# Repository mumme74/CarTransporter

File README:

Abstraction layer for EEPROM ICs like 25AA/25LC (SPI).

1. DESCRIPTION

This library designed to work on top of ChibiOS/RT. It abstracts access to
EEPROM like a regular file(s).

2. LIMITATIONS

* SPI Only.

3. USAGE

* Include eeprom.h file to your project.
* Modify eeprom_conf.h for your project.
* Define file object of an EepromFileStream type and config structure for it.
* Open it with EepromOpen() function.

Now you can access to EEPROM array like to a regular file with functions:
- chFileStreamRead()
- chFileStreamWrite()
- chFileStreamGetPosition()
- chFileStreamSeek()
etc.

Examples of usage and checking the returning parameter you can found in
eeprom_testsuit.c

Based on 24aa project of ChibiOS/RT from Uladzimir Pylinski (aka barthess):
https://github.com/barthess/24aa

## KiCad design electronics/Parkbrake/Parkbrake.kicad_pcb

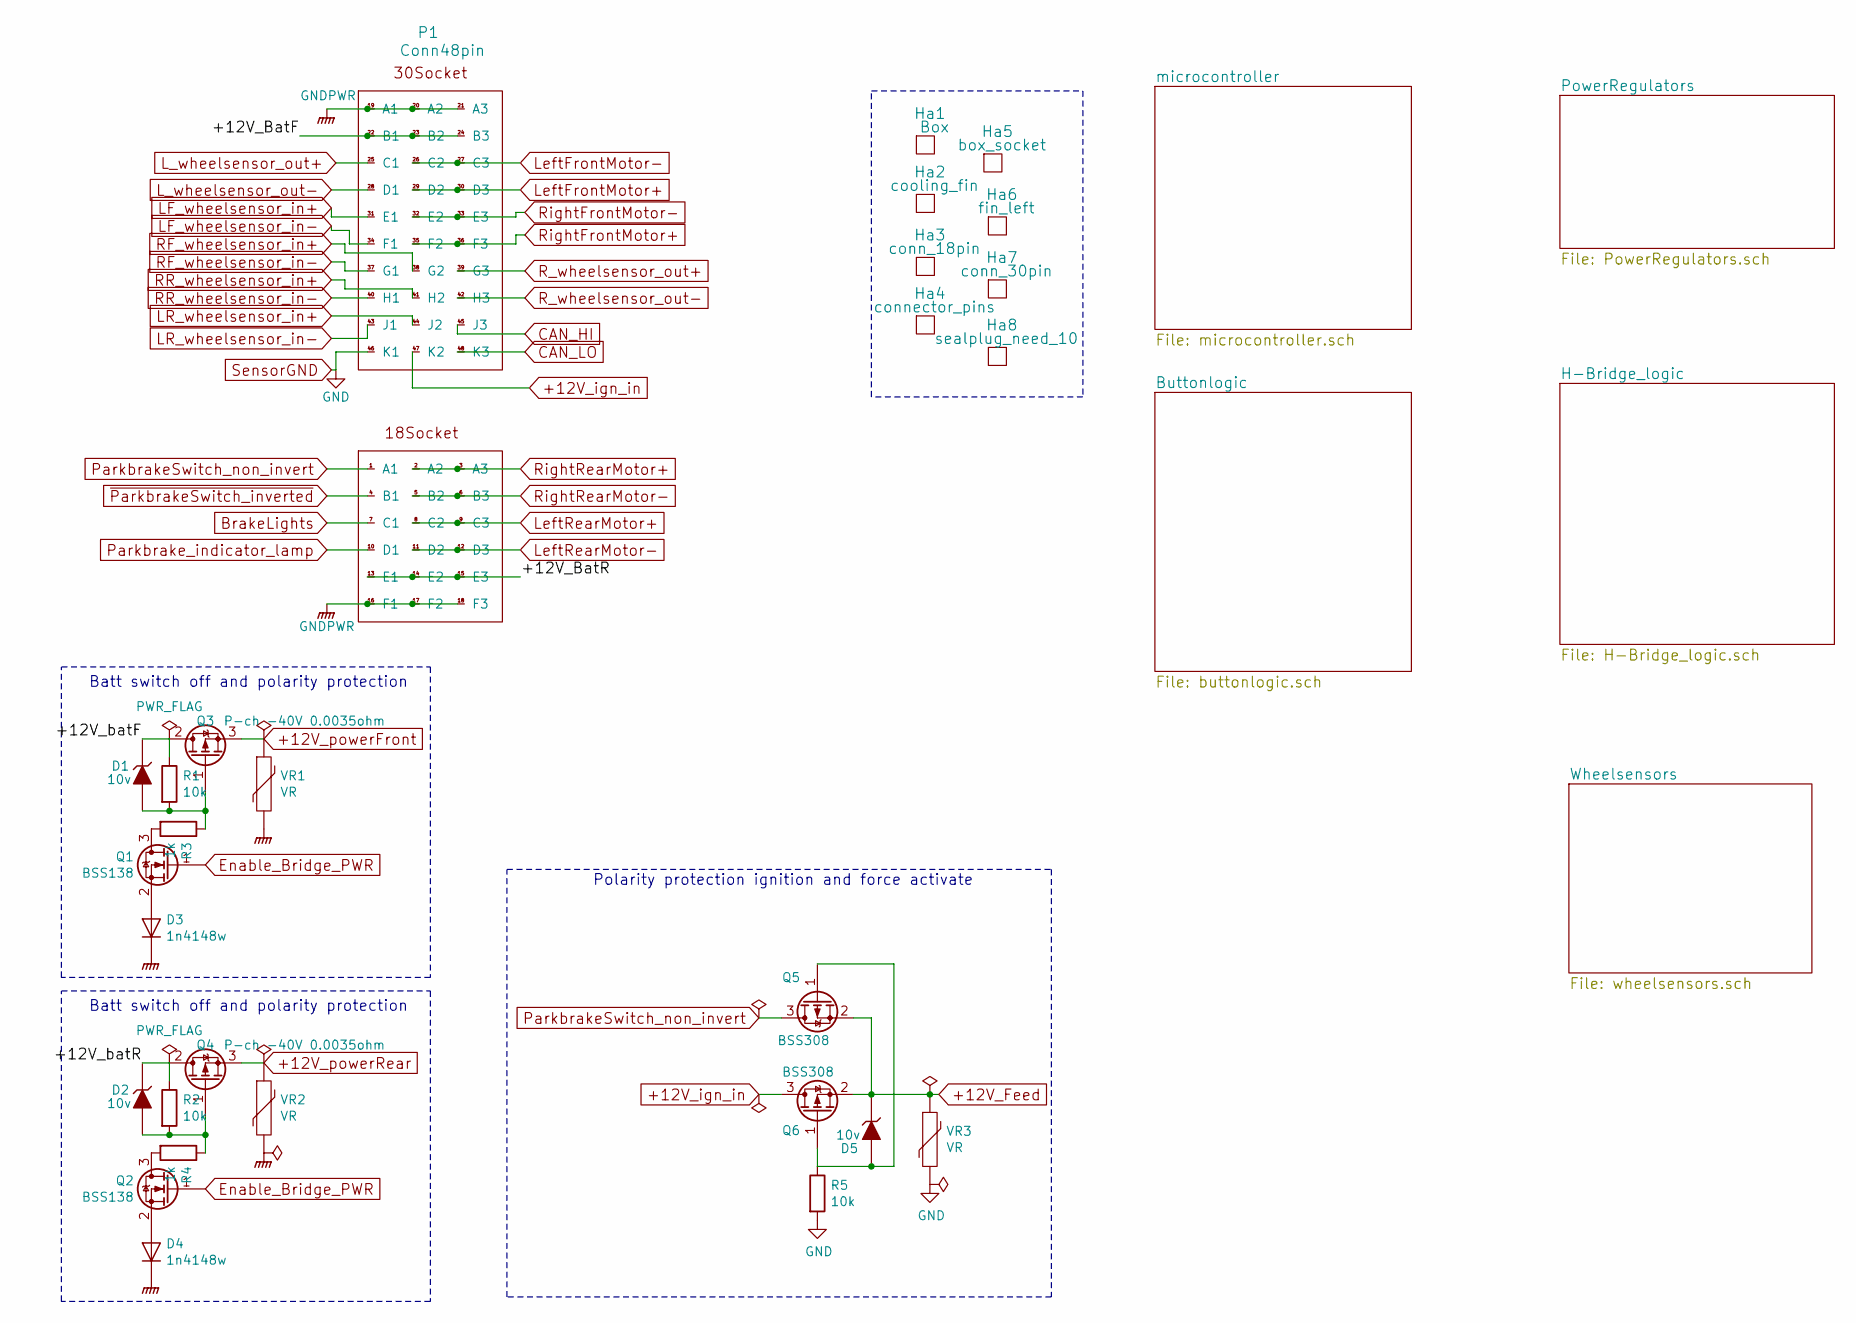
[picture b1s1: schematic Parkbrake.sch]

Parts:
D1, D2, D5: 10v; SOD-323; part MM3Z10VT1G; farnell 1431190
D3, D4: 1n4148w; SOD-323; part 1N4148WS; farnell 1466524
Ha1: Box; part 5810130042; farnell 1282197
Ha2: cooling_fin; part 5810000021; farnell 1282203
Ha3: conn_18pin; part 581-01-18-023; farnell 2099333
Ha4: connector_pins; part 4250000872; farnell 1282209
Ha5: box_socket; part 5810148007; farnell 1282184
Ha6: fin_left; part 5810000020; farnell 1282204
Ha7: conn_30pin; part 581-01-30-029; farnell 2143771
Ha8: sealplug_need_10; part 581-00-00-011; farnell 2099332
P1: Conn48pin
Q1, Q2: BSS138; SOT-323; part BSS138PW; farnell 1907611
Q3, Q4: P-ch -40V 0.0035ohm; TO-252-2Lead; part PD90P04P4-05; farnell 2480840
Q5, Q6: BSS308; SOT-23; part BSS308PE H6327; farnell 2432719
R1, R2, R5: 10k; R_0805; part MC01W0805110K; farnell 9332391
R3, R4: 1k; R_0805; part MC01W080511K; farnell 9332383
VR1, VR2, VR3: VR; R_1206; part VCAS120614A300DP; farnell 2346678

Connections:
+12V_Feed: D5.1 (K), Q5.2 (S), Q6.2 (S), VR3.1; also elsewhere on the board
+12V_ign_in: P1.47 (K2), Q6.3 (D); also elsewhere on the board
+12V_powerFront: Q3.3 (S), VR1.1; also elsewhere on the board
+12V_powerRear: Q4.3 (S), VR2.1; also elsewhere on the board
/+12V_BatF: D1.1 (K), P1.22 (B1), P1.23 (B2), P1.24 (B3), Q3.2 (D), R1.1
/+12V_BatR: D2.1 (K), P1.13 (E1), P1.14 (E2), P1.15 (E3), Q4.2 (D), R2.1
BrakeLights: P1.7 (C1); also elsewhere on the board
CAN_HI: P1.45 (J3); also elsewhere on the board
CAN_LO: P1.48 (K3); also elsewhere on the board
Enable_Bridge_PWR: Q1.1 (G), Q2.1 (G); also elsewhere on the board
GNDPWR: D3.1 (K), D4.1 (K), P1.16 (F1), P1.17 (F2), P1.18 (F3), P1.19 (A1), P1.20 (A2), P1.21 (A3), VR1.2, VR2.2; also elsewhere on the board
LF_wheelsensor_in+: P1.31 (E1); also elsewhere on the board
LF_wheelsensor_in-: P1.34 (F1); also elsewhere on the board
LR_wheelsensor_in+: P1.44 (J2); also elsewhere on the board
LR_wheelsensor_in-: P1.40 (H1), P1.43 (J1), P1.46 (K1), R5.2, VR3.2; also elsewhere on the board
L_wheelsensor_out+: P1.25 (C1); also elsewhere on the board
L_wheelsensor_out-: P1.28 (D1); also elsewhere on the board
LeftFrontMotor+: P1.29 (D2), P1.30 (D3); also elsewhere on the board
LeftFrontMotor-: P1.26 (C2), P1.27 (C3); also elsewhere on the board
LeftRearMotor+: P1.8 (C2), P1.9 (C3); also elsewhere on the board
LeftRearMotor-: P1.11 (D2), P1.12 (D3); also elsewhere on the board
unnamed: D1.2 (A), Q3.1 (G), R1.2, R3.1
unnamed: D2.2 (A), Q4.1 (G), R2.2, R4.1
unnamed: D3.2 (A), Q1.2 (S)
unnamed: D4.2 (A), Q2.2 (S)
unnamed: D5.2 (A), Q5.1 (G), Q6.1 (G), R5.1
unnamed: Q1.3 (D), R3.2
unnamed: Q2.3 (D), R4.2
ParkbrakeSwitch_non_invert: P1.1 (A1), Q5.3 (D); also elsewhere on the board
Parkbrake_indicator_lamp: P1.10 (D1); also elsewhere on the board
RF_wheelsensor_in+: P1.38 (G2); also elsewhere on the board
RF_wheelsensor_in-: P1.37 (G1); also elsewhere on the board
RR_wheelsensor_in+: P1.41 (H2); also elsewhere on the board
R_wheelsensor_out+: P1.39 (G3); also elsewhere on the board
R_wheelsensor_out-: P1.42 (H3); also elsewhere on the board
RightFrontMotor+: P1.35 (F2), P1.36 (F3); also elsewhere on the board
RightFrontMotor-: P1.32 (E2), P1.33 (E3); also elsewhere on the board
RightRearMotor+: P1.2 (A2), P1.3 (A3); also elsewhere on the board
RightRearMotor-: P1.5 (B2), P1.6 (B3); also elsewhere on the board
~ParkbrakeSwitch_inverted: P1.4 (B1); also elsewhere on the board

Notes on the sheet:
Batt switch off and polarity protection
Polarity protection ignition and force activate

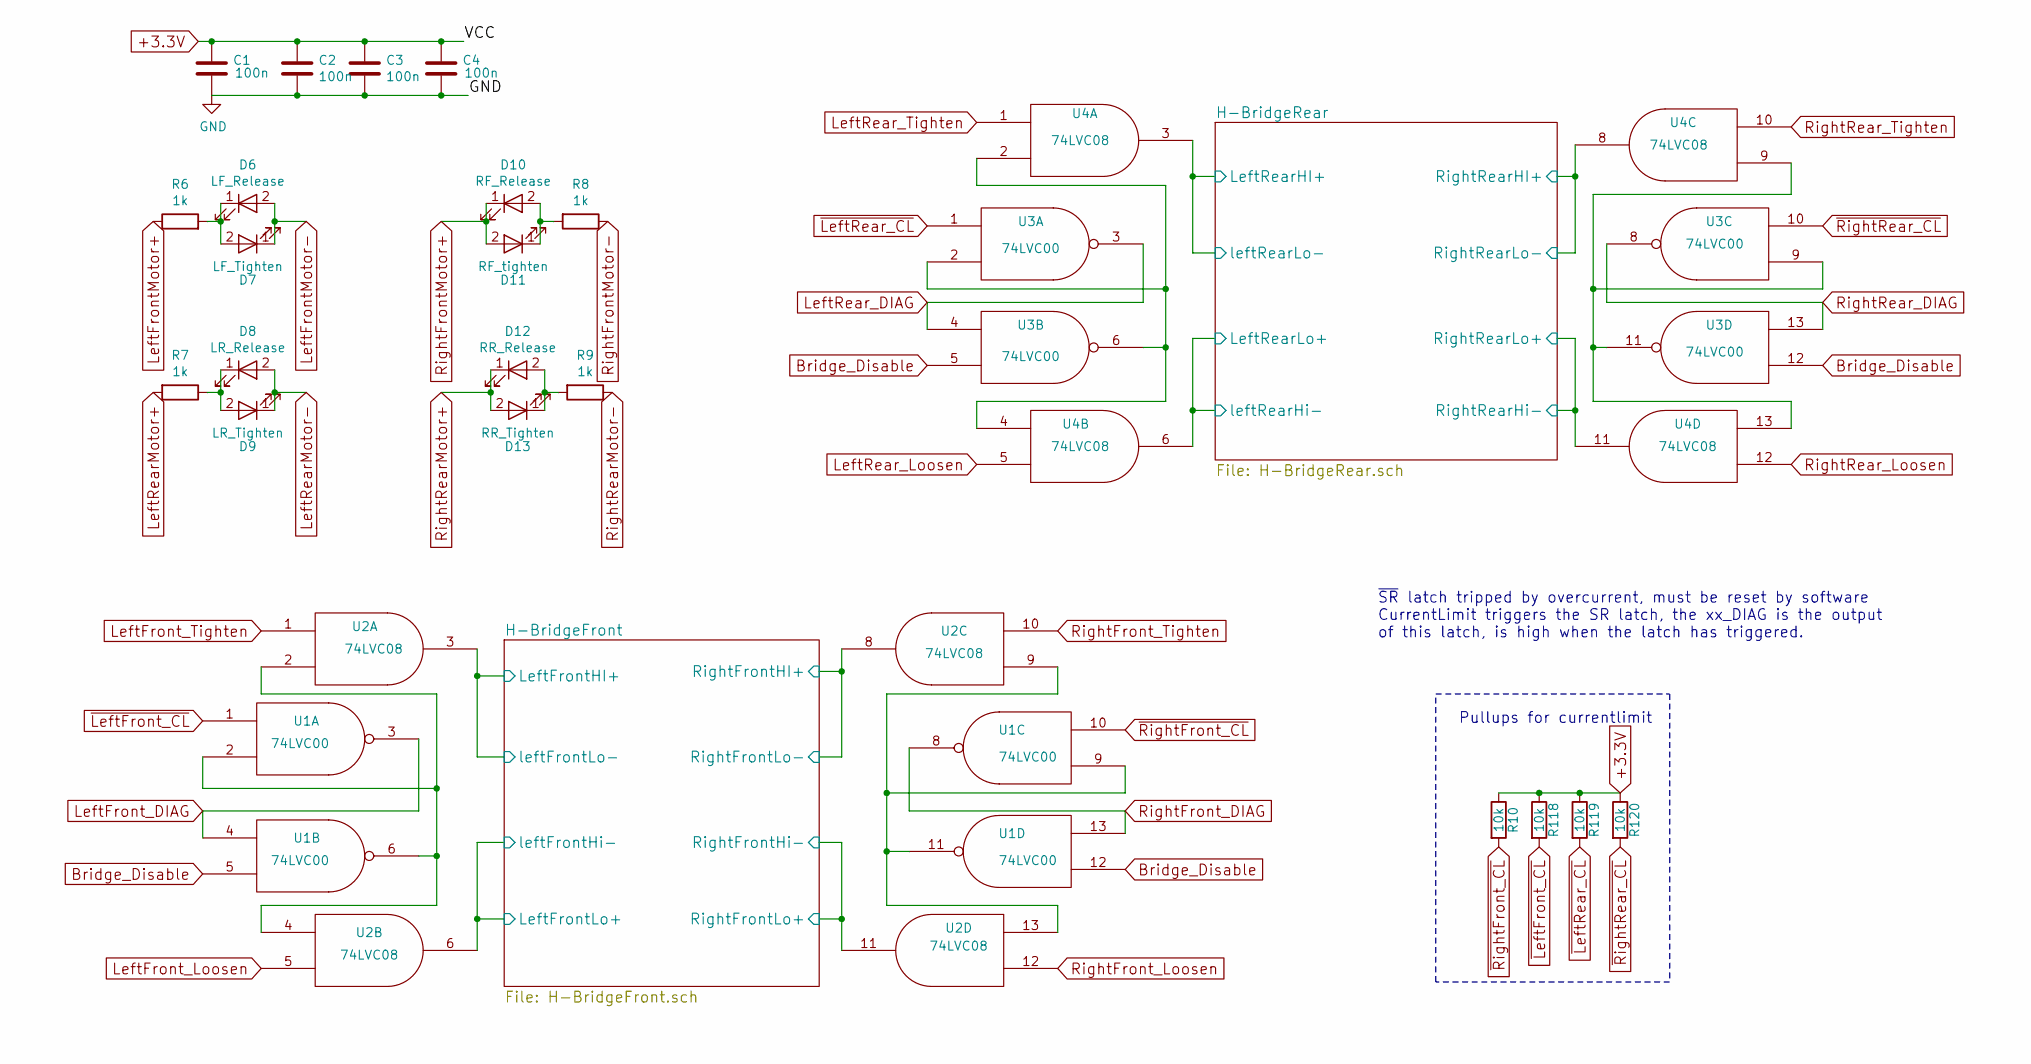
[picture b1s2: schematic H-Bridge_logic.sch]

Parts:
C1, C2, C3, C4: 100n; C_0805; part 0805B104J500CT; farnell 2496940
D6: LF_Release; LED_0805; part KP-2012LSGC; farnell 2463991
D7: LF_Tighten; LED_0805; part KP-2012SRC-PRV; farnell 1318244
D8: LR_Release; LED_0805; part KP-2012LSGC; farnell 2463991
D9: LR_Tighten; LED_0805; part KP-2012SRC-PRV; farnell 1318244
D10: RF_Release; LED_0805; part KP-2012LSGC; farnell 2463991
D11: RF_tighten; LED_0805; part KP-2012SRC-PRV; farnell 1318244
D12: RR_Release; LED_0805; part KP-2012LSGC; farnell 2463991
D13: RR_Tighten; LED_0805; part KP-2012SRC-PRV; farnell 1318244
R6, R7, R8, R9: 1k; R_0805; part MC01W080511K; farnell 9332383
R10, R118, R119, R120: 10k; R_0805; part MC01W0805110K; farnell 9332391
U1, U3: 74LVC00; TSSOP-14_4.4x5mm_Pitch0.65mm; part SN74LVC00APWR; farnell 1105931
U2, U4: 74LVC08; TSSOP-14_4.4x5mm_Pitch0.65mm; part 74LVC08APW-Q100.11; farnell 2445097

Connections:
+3.3V: C1.1, C2.1, C3.1, C4.1, R10.1, R118.1, R119.1, R120.1, U1.14 (VCC), U2.14 (VCC), U3.14 (VCC), U4.14 (VCC); also elsewhere on the board
/H-Bridge_logic/H-BridgeFront/LeftFrontHI+: U2.3; also elsewhere on the board
/H-Bridge_logic/H-BridgeFront/LeftFrontLo+: U2.6; also elsewhere on the board
/H-Bridge_logic/H-BridgeFront/RightFrontHI+: U2.8; also elsewhere on the board
/H-Bridge_logic/H-BridgeFront/RightFrontHi-: U2.11; also elsewhere on the board
/H-Bridge_logic/H-BridgeRear/LeftRearHI+: U4.3; also elsewhere on the board
/H-Bridge_logic/H-BridgeRear/LeftRearLo+: U4.6; also elsewhere on the board
/H-Bridge_logic/H-BridgeRear/RightRearHI+: U4.8; also elsewhere on the board
/H-Bridge_logic/H-BridgeRear/RightRearHi-: U4.11; also elsewhere on the board
Bridge_Disable: U1.5, U1.12, U3.5, U3.12; also elsewhere on the board
LR_wheelsensor_in-: C1.2, C2.2, C3.2, C4.2, U1.7 (GND), U2.7 (GND), U3.7 (GND), U4.7 (GND); also elsewhere on the board
LeftFrontMotor+: R6.1; also elsewhere on the board
LeftFrontMotor-: D6.2 (A), D7.1 (K); also elsewhere on the board
LeftFront_DIAG: U1.3, U1.4; also elsewhere on the board
LeftFront_Loosen: U2.5; also elsewhere on the board
LeftFront_Tighten: U2.1; also elsewhere on the board
LeftRearMotor+: R7.2; also elsewhere on the board
LeftRearMotor-: D8.2 (A), D9.1 (K); also elsewhere on the board
LeftRear_DIAG: U3.3, U3.4; also elsewhere on the board
LeftRear_Loosen: U4.5; also elsewhere on the board
LeftRear_Tighten: U4.1; also elsewhere on the board
unnamed: D6.1 (K), D7.2 (A), R6.2
unnamed: D8.1 (K), D9.2 (A), R7.1
unnamed: D10.2 (A), D11.1 (K), R8.2
unnamed: D12.2 (A), D13.1 (K), R9.2
unnamed: U1.2, U1.6, U2.2, U2.4
unnamed: U1.9, U1.11, U2.9, U2.13
unnamed: U3.2, U3.6, U4.2, U4.4
unnamed: U3.9, U3.11, U4.9, U4.13
RightFrontMotor+: D10.1 (K), D11.2 (A); also elsewhere on the board
RightFrontMotor-: R8.1; also elsewhere on the board
RightFront_DIAG: U1.8, U1.13; also elsewhere on the board
RightFront_Loosen: U2.12; also elsewhere on the board
RightFront_Tighten: U2.10; also elsewhere on the board
RightRearMotor+: D12.1 (K), D13.2 (A); also elsewhere on the board
RightRearMotor-: R9.1; also elsewhere on the board
RightRear_DIAG: U3.8, U3.13; also elsewhere on the board
RightRear_Loosen: U4.12; also elsewhere on the board
RightRear_Tighten: U4.10; also elsewhere on the board
~LeftFront_CL: R118.2, U1.1; also elsewhere on the board
~LeftRear_CL: R119.2, U3.1; also elsewhere on the board
~RightFront_CL: R10.2, U1.10; also elsewhere on the board
~RightRear_CL: R120.2, U3.10; also elsewhere on the board

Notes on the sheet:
~SR~ latch tripped by overcurrent, must be reset by software CurrentLimit triggers the SR latch, the xx_DIAG is the output of this latch, is high when the latch has triggered.
Pullups for currentlimit

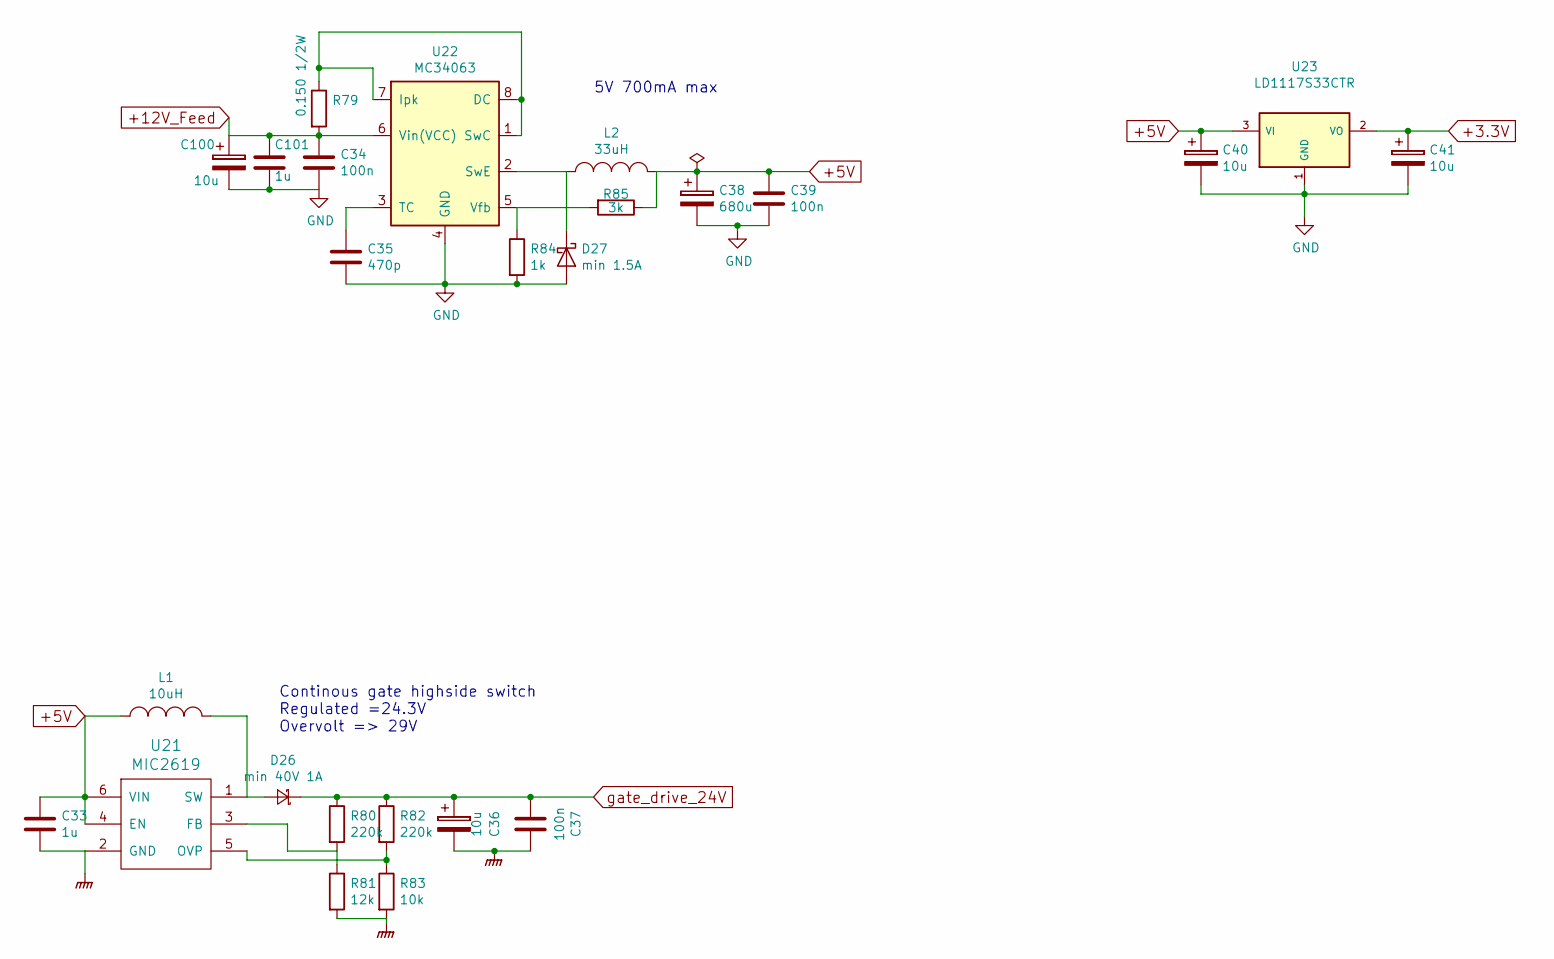
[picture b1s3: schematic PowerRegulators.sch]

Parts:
C33, C101: 1u; C_1206; part GRM31MR71E105JA01L; farnell 2362126
C34, C37, C39: 100n; C_0805; part 0805B104J500CT; farnell 2496940
C35: 470p; C_0805; part 0805N471J500CT; farnell 2497037
C36: 10u; TantalC_SizeC_EIA-6032_Wave; part T491C106K035AT; farnell 1457464
C38: 680u; TantalC_SizeD_EIA-7343_Wave; part TPSE687K006R0060; farnell 2283882
C40, C41, C100: 10u; CP_0805; part TMCP0J106KTRF; farnell 2491430
D26: min 40V 1A; SOD-123; part NTS260SFT1G; farnell 2473419
D27: min 1.5A; SOD-123; part NTS260SFT1G; farnell 2473419
L1: 10uH; inductor_sd54; part LQH32CN100K33L; farnell 9522204
L2: 33uH; inductor_sd54; part SD54-333MLB; farnell 2526983
R79: 0.150 1/2W; R_1206; part WW12PR150FTL; farnell 2503066
R80, R82: 220k; R_0805; part MC01W08051220K; farnell 9332839
R81: 12k; R_0805; part MC01W0805112K; farnell 9332502
R83: 10k; R_0805; part MC01W0805110K; farnell 9332391
R84: 1k; R_0805; part MC01W080511K; farnell 9332383
R85: 3k; R_0805; part MC01W080513K; farnell 9332995
U21: MIC2619; SOT-23-6; part MIC2619YD6-TR; farnell 2509963
U22: MC34063; SOIC-8_3.9x4.9mm_Pitch1.27mm; part MC34063ABD-TR; farnell 1087205
U23: LD1117S33CTR; SOT-223; part LD1117S33CTR; farnell 1467779

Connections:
+3.3V: C41.1, U23.2 (VO); also elsewhere on the board
+5V: C33.1, C38.1, C39.1, C40.1, L1.1, L2.2, R85.1, U21.4 (EN), U21.6 (VIN), U23.3 (VI); also elsewhere on the board
+12V_Feed: C34.1, C100.1, C101.1, R79.2, U22.6 (Vin(VCC)); also elsewhere on the board
GNDPWR: C33.2, C36.2, C37.1, R81.2, R83.2, U21.2 (GND); also elsewhere on the board
LR_wheelsensor_in-: C34.2, C35.2, C38.2, C39.2, C40.2, C41.2, C100.2, C101.2, D27.2 (A), R84.2, U22.4 (GND), U23.1 (GND); also elsewhere on the board
unnamed: C35.1, U22.3 (TC)
unnamed: D26.2 (A), L1.2, U21.1 (SW)
unnamed: D27.1 (K), L2.1, U22.2 (SwE)
unnamed: R79.1, U22.1 (SwC), U22.7 (Ipk), U22.8 (DC)
unnamed: R80.2, R81.1, U21.3 (FB)
unnamed: R82.2, R83.1, U21.5 (OVP)
unnamed: R84.1, R85.2, U22.5 (Vfb)
gate_drive_24V: C36.1, C37.2, D26.1 (K), R80.1, R82.1; also elsewhere on the board

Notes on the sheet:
Continous gate highside switch Regulated =24.3V Overvolt => 29V
5V 700mA max

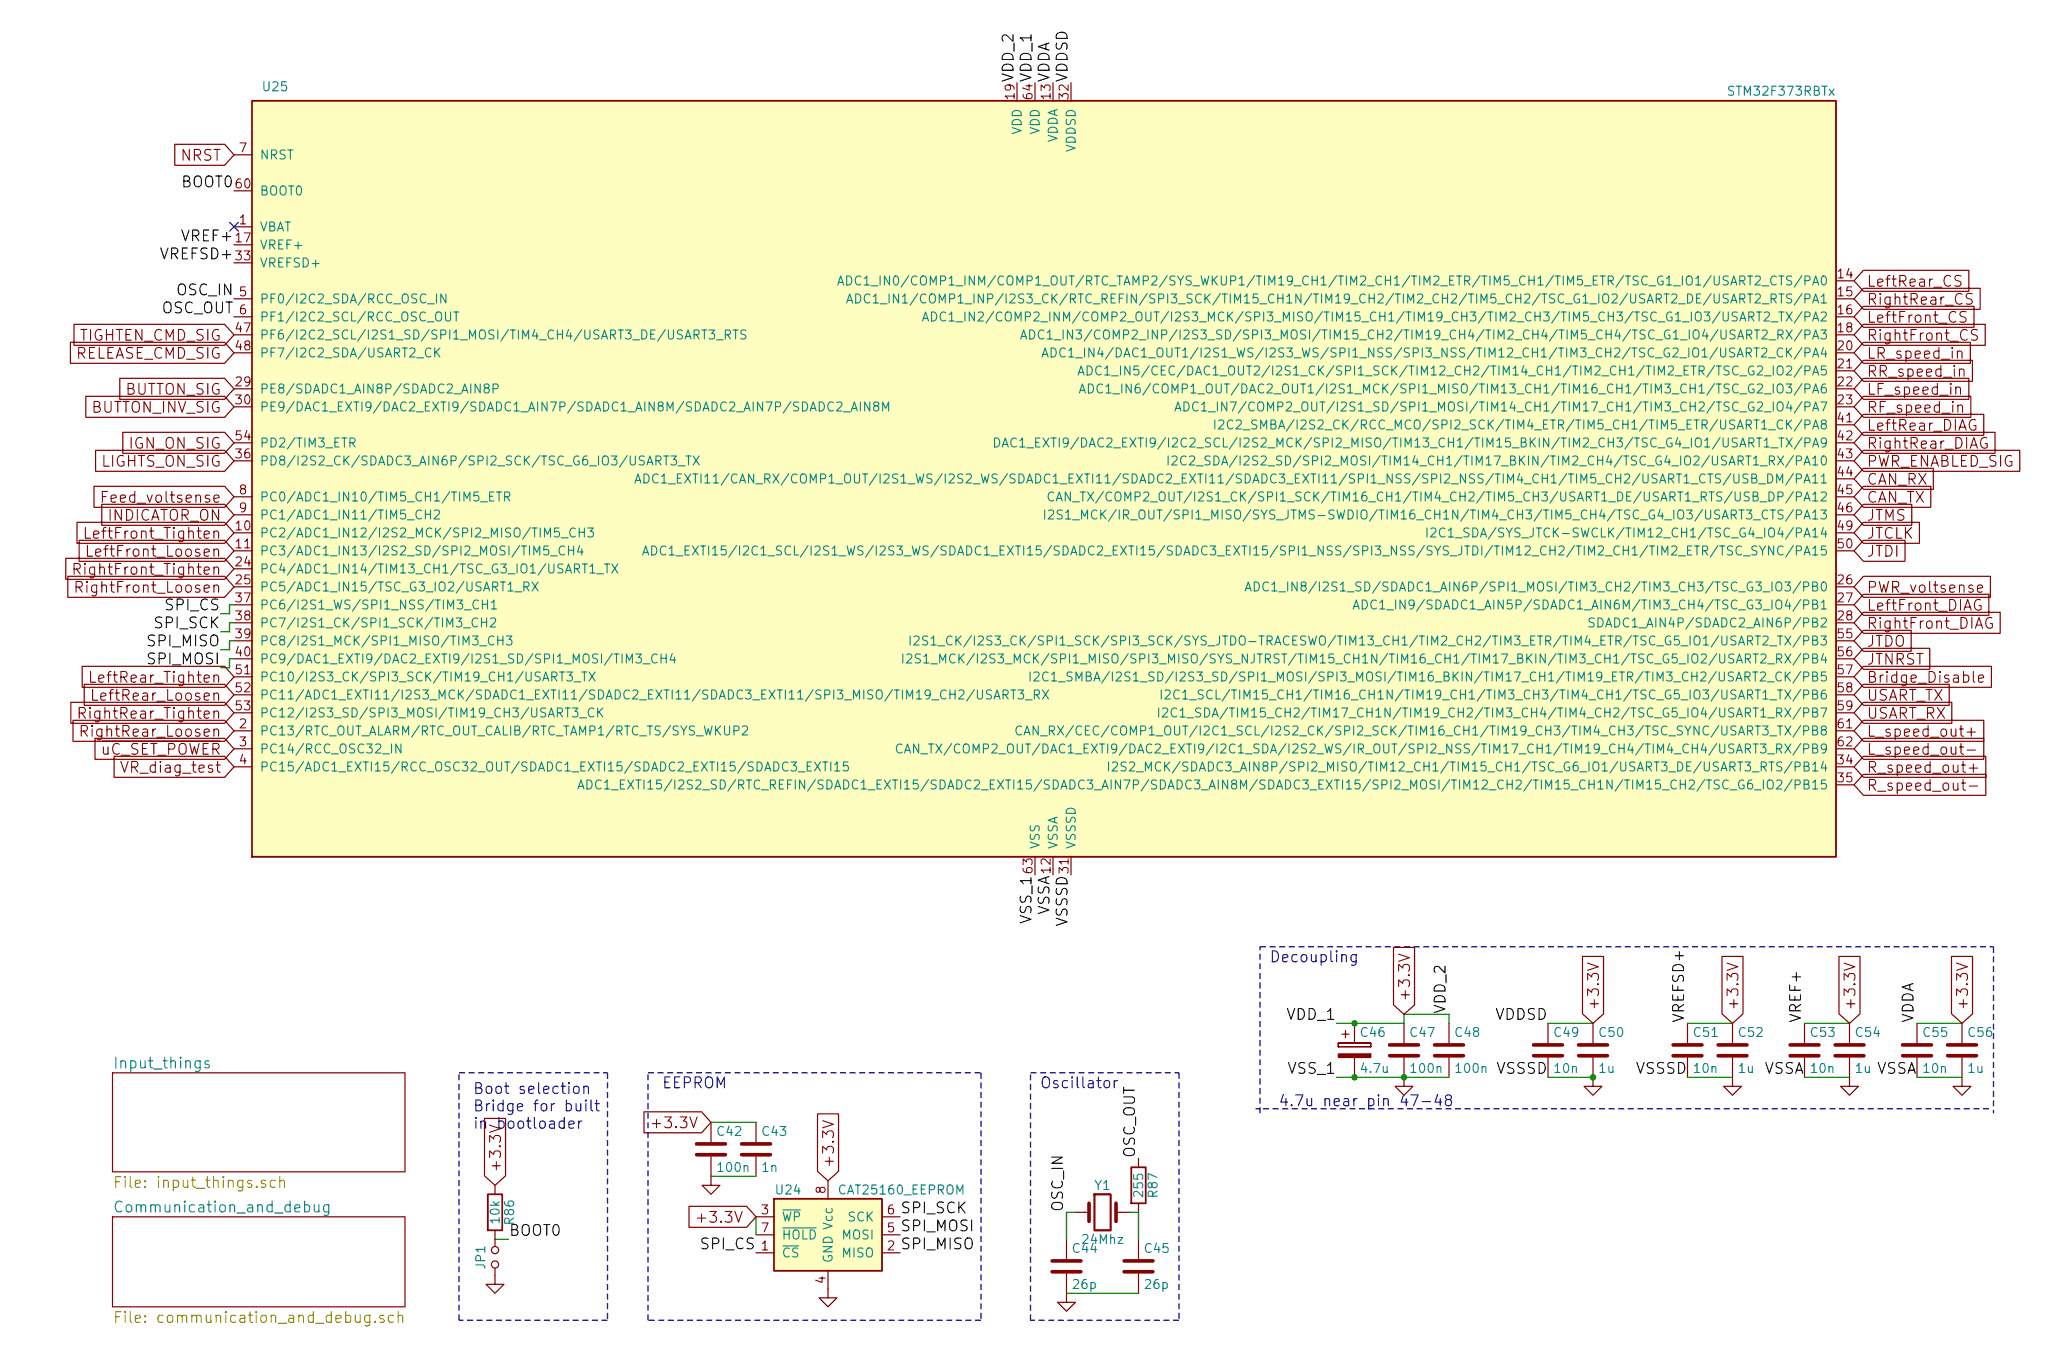
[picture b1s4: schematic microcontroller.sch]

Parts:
C42, C47, C48: 100n; C_0805; part 0805B104J500CT; farnell 2496940
C43: 1n; C_0805; part GRM2165C1H102JA01D; farnell 2494247
C44, C45: 26p; C_0805; part 0805N270J500CT; farnell 2497027
C46: 4.7u; CP_0805; part TMCP0J475KTRF; farnell 2491429
C49, C51, C53, C55: 10n; C_0805; part 0805B103J500CT; farnell 2496936
C50, C52, C54, C56: 1u; C_1206; part GRM31MR71E105JA01L; farnell 2362126
JP1: BOOT0; R_0805_HandSoldering; part RC1206JR-070RL; farnell 9240276
R86: 10k; R_0805; part MC01W0805110K; farnell 9332391
R87: 255; R_0805; part ERJ6ENF2550V; farnell 2303484
U24: CAT25160_EEPROM; TSSOP-8_4.4x3mm_Pitch0.65mm; part CAT25160YI-GT3; farnell 2534647
U25: STM32F373RBTx; LQFP-64_10x10mm_Pitch0.5mm; part STM32F373RBT6; farnell 2333277
Y1: 24Mhz; ABM3; part ABM3-24.000MHZ-D2Y-T; farnell 2467794

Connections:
+3.3V: C42.1, C43.1, C46.1, C47.1, C48.1, C49.1, C50.1, C51.1, C52.1, C53.1, C54.1, C55.1, C56.1, R86.1, U24.3 (~WP), U24.7 (~HOLD), U24.8 (Vcc), U25.13 (VDDA), U25.17 (VREF+), U25.19 (VDD), U25.32 (VDDSD), U25.33 (VREFSD+), U25.64 (VDD); also elsewhere on the board
/microcontroller/BOOT0: JP1.2, R86.2, U25.60 (BOOT0)
/microcontroller/OSC_IN: C44.1, U25.5 (PF0/I2C2_SDA/RCC_OSC_IN), Y1.1
/microcontroller/OSC_OUT: R87.1, U25.6 (PF1/I2C2_SCL/RCC_OSC_OUT)
/microcontroller/SPI_CS: U24.1 (~CS), U25.37 (PC6/I2S1_WS/SPI1_NSS/TIM3_CH1)
/microcontroller/SPI_MISO: U24.2 (MISO), U25.39 (PC8/I2S1_MCK/SPI1_MISO/TIM3_CH3)
/microcontroller/SPI_MOSI: U24.5 (MOSI), U25.40 (PC9/DAC1_EXTI9/DAC2_EXTI9/I2S1_SD/SPI1_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)
/microcontroller/SPI_SCK: U24.6 (SCK), U25.38 (PC7/I2S1_CK/SPI1_SCK/TIM3_CH2)
BUTTON_INV_SIG: U25.30 (PE9/DAC1_EXTI9/DAC2_EXTI9/SDADC1_AIN7P/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); also elsewhere on the board
BUTTON_SIG: U25.29 (PE8/SDADC1_AIN8P/SDADC2_AIN8P); also elsewhere on the board
Bridge_Disable: U25.57 (I2C1_SMBA/I2S1_SD/I2S3_SD/SPI1_MOSI/SPI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); also elsewhere on the board
CAN_RX: U25.44 (ADC1_EXTI11/CAN_RX/COMP1_OUT/I2S1_WS/I2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); also elsewhere on the board
CAN_TX: U25.45 (CAN_TX/COMP2_OUT/I2S1_CK/SPI1_SCK/TIM16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); also elsewhere on the board
Feed_voltsense: U25.8 (PC0/ADC1_IN10/TIM5_CH1/TIM5_ETR); also elsewhere on the board
IGN_ON_SIG: U25.54 (PD2/TIM3_ETR); also elsewhere on the board
INDICATOR_ON: U25.9 (PC1/ADC1_IN11/TIM5_CH2); also elsewhere on the board
JTCLK: U25.49 (I2C1_SDA/SYS_JTCK-SWCLK/TIM12_CH1/TSC_G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); also elsewhere on the board
JTDI: U25.50 (ADC1_EXTI15/I2C1_SCL/I2S1_WS/I2S3_WS/SD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); also elsewhere on the board
JTDO: U25.55 (I2S1_CK/I2S3_CK/SPI1_SCK/SPI3_SCK/SYS_J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); also elsewhere on the board
JTMS: U25.46 (I2S1_MCK/IR_OUT/SPI1_MISO/SYS_JTMS-SWDI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); also elsewhere on the board
JTNRST: U25.56 (I2S1_MCK/I2S3_MCK/SPI1_MISO/SPI3_MISO/S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); also elsewhere on the board
LF_speed_in: U25.22 (ADC1_IN6/COMP1_OUT/DAC2_OUT1/I2S1_MCK/S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); also elsewhere on the board
LIGHTS_ON_SIG: U25.36 (PD8/I2S2_CK/SDADC3_AIN6P/SPI2_SCK/TSC_G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); also elsewhere on the board
LR_speed_in: U25.20 (ADC1_IN4/DAC1_OUT1/I2S1_WS/I2S3_WS/SPI1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); also elsewhere on the board
LR_wheelsensor_in-: C42.2, C43.2, C44.2, C45.2, C46.2, C47.2, C48.2, C49.2, C50.2, C51.2, C52.2, C53.2, C54.2, C55.2, C56.2, JP1.1, U24.4 (GND), U25.12 (VSSA), U25.31 (VSSSD), U25.63 (VSS); also elsewhere on the board
L_speed_out+: U25.61 (CAN_RX/CEC/COMP1_OUT/I2C1_SCL/I2S2_CK/S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); also elsewhere on the board
L_speed_out-: U25.62 (CAN_TX/COMP2_OUT/DAC1_EXTI9/DAC2_EXTI9/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); also elsewhere on the board
LeftFront_CS: U25.16 (ADC1_IN2/COMP2_INM/COMP2_OUT/I2S3_MCK/S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); also elsewhere on the board
LeftFront_DIAG: U25.27 (ADC1_IN9/SDADC1_AIN5P/SDADC1_AIN6M/TIM3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); also elsewhere on the board
LeftFront_Loosen: U25.11 (PC3/ADC1_IN13/I2S2_SD/SPI2_MOSI/TIM5_CH4); also elsewhere on the board
LeftFront_Tighten: U25.10 (PC2/ADC1_IN12/I2S2_MCK/SPI2_MISO/TIM5_C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); also elsewhere on the board
LeftRear_CS: U25.14 (ADC1_IN0/COMP1_INM/COMP1_OUT/RTC_TAMP2/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); also elsewhere on the board
LeftRear_DIAG: U25.41 (I2C2_SMBA/I2S2_CK/RCC_MCO/SPI2_SCK/TIM4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); also elsewhere on the board
LeftRear_Loosen: U25.52 (PC11/ADC1_EXTI11/I2S3_MCK/SDADC1_EXTI11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); also elsewhere on the board
LeftRear_Tighten: U25.51 (PC10/I2S3_CK/SPI3_SCK/TIM19_CH1/USART3_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); also elsewhere on the board
NRST: U25.7 (NRST); also elsewhere on the board
unnamed: C45.1, R87.2, Y1.2
PWR_ENABLED_SIG: U25.43 (I2C2_SDA/I2S2_SD/SPI2_MOSI/TIM14_CH1/TI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); also elsewhere on the board
PWR_voltsense: U25.26 (ADC1_IN8/I2S1_SD/SDADC1_AIN6P/SPI1_MOSI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); also elsewhere on the board
RELEASE_CMD_SIG: U25.48 (PF7/I2C2_SDA/USART2_CK); also elsewhere on the board
RF_speed_in: U25.23 (ADC1_IN7/COMP2_OUT/I2S1_SD/SPI1_MOSI/TI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); also elsewhere on the board
RR_speed_in: U25.21 (ADC1_IN5/CEC/DAC1_OUT2/I2S1_CK/SPI1_SCK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); also elsewhere on the board
R_speed_out+: U25.34 (I2S2_MCK/SDADC3_AIN8P/SPI2_MISO/TIM12_C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); also elsewhere on the board
R_speed_out-: U25.35 (ADC1_EXTI15/I2S2_SD/RTC_REFIN/SDADC1_EX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); also elsewhere on the board
RightFront_CS: U25.18 (ADC1_IN3/COMP2_INP/I2S3_SD/SPI3_MOSI/TI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); also elsewhere on the board
RightFront_DIAG: U25.28 (SDADC1_AIN4P/SDADC2_AIN6P/PB2); also elsewhere on the board
RightFront_Loosen: U25.25 (PC5/ADC1_IN15/TSC_G3_IO2/USART1_RX); also elsewhere on the board
RightFront_Tighten: U25.24 (PC4/ADC1_IN14/TIM13_CH1/TSC_G3_IO1/USAR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); also elsewhere on the board
RightRear_CS: U25.15 (ADC1_IN1/COMP1_INP/I2S3_CK/RTC_REFIN/SP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); also elsewhere on the board
RightRear_DIAG: U25.42 (DAC1_EXTI9/DAC2_EXTI9/I2C2_SCL/I2S2_MCK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); also elsewhere on the board
RightRear_Loosen: U25.2 (PC13/RTC_OUT_ALARM/RTC_OUT_CALIB/RTC_TA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); also elsewhere on the board
RightRear_Tighten: U25.53 (PC12/I2S3_SD/SPI3_MOSI/TIM19_CH3/USART3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); also elsewhere on the board
TIGHTEN_CMD_SIG: U25.47 (PF6/I2C2_SCL/I2S1_SD/SPI1_MOSI/TIM4_CH4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); also elsewhere on the board
USART_RX: U25.59 (I2C1_SDA/TIM15_CH2/TIM17_CH1N/TIM19_CH2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); also elsewhere on the board
USART_TX: U25.58 (I2C1_SCL/TIM15_CH1/TIM16_CH1N/TIM19_CH1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); also elsewhere on the board
VR_diag_test: U25.4 (PC15/ADC1_EXTI15/RCC_OSC32_OUT/SDADC1_E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); also elsewhere on the board
~uC_SET_POWER: U25.3 (PC14/RCC_OSC32_IN); also elsewhere on the board

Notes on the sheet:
4.7u near pin 47-48
Oscillator
Decoupling
Boot selection Bridge for built in bootloader
EEPROM

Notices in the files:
firmware/parkbrake_ECU/board/board.h:
ChibiOS - Copyright (C) 2006..2016 Giovanni Di Sirio
Licensed under the Apache License, Version 2.0 (the "License");
